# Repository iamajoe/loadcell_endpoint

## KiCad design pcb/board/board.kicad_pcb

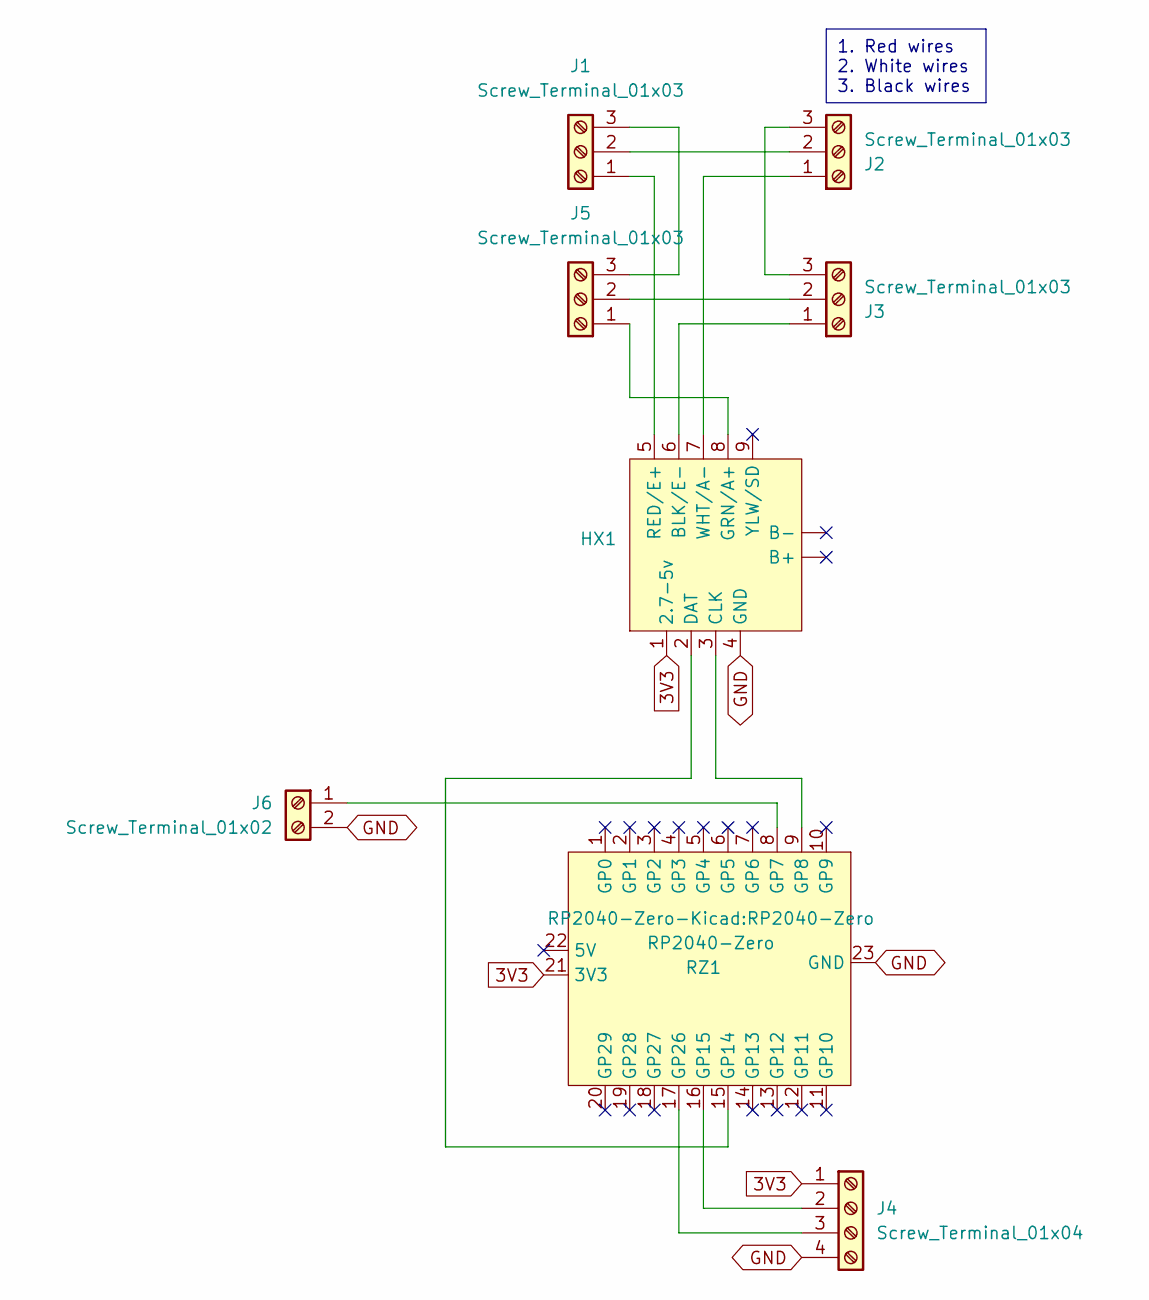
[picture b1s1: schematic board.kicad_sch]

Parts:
HX1: hx711_module
J1, J2, J3, J5: Screw_Terminal_01x03; JST_XH_B3B-XH-A_1x03_P2.50mm_Vertical
J4: Screw_Terminal_01x04; JST_XH_B4B-XH-A_1x04_P2.50mm_Vertical
J6: Screw_Terminal_01x02; JST_XH_B2B-XH-A_1x02_P2.50mm_Vertical
RZ1: RP2040-Zero

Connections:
3V3: HX1.1 (2.7-5v), J4.1, RZ1.21 (3V3)
GND: HX1.4 (GND), J4.4, J6.2, RZ1.23 (GND)
unnamed: HX1.6 (BLK/E-), J3.1
unnamed: HX1.3 (CLK), RZ1.9 (GP8)
unnamed: HX1.2 (DAT), RZ1.15 (GP14)
unnamed: HX1.8 (GRN/A+), J5.1
unnamed: HX1.5 (RED/E+), J1.1
unnamed: HX1.7 (WHT/A-), J2.1
unnamed: J1.2, J2.2
unnamed: J1.3, J5.3
unnamed: J2.3, J3.3
unnamed: J3.2, J5.2
unnamed: J4.2, RZ1.16 (GP15)
unnamed: J4.3, RZ1.17 (GP26)
unnamed: J6.1, RZ1.8 (GP7)

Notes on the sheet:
1. Red wires 2. White wires 3. Black wires

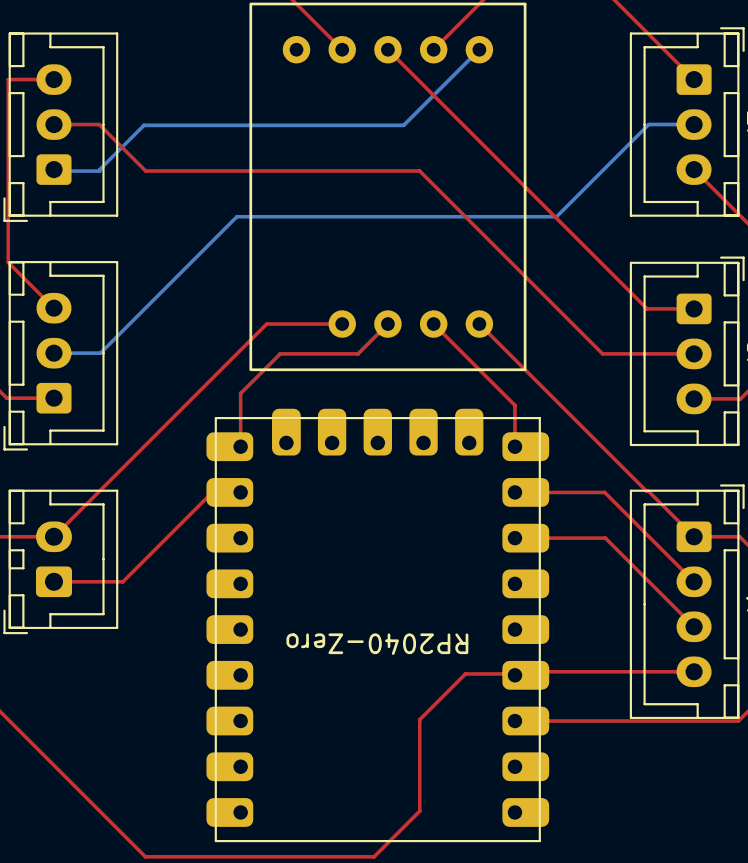
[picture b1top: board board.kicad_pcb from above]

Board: 2 copper layers, 8 parts (0 on the bottom side), 15 nets.

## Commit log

2025-04-06 setup core and tests
2025-04-06 implement calibrate
2025-04-06 setup the calibration methods
2025-04-06 move from usize to f32 values
2025-04-12 wip work on the load cell part
2025-04-12 tweak and use the load cell
2025-04-12 tweak and improve usage of outputs
2025-04-12 remove unnecessary folders
